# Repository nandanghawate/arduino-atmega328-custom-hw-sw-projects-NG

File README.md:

# atmega328-door-status-alarm-NG
# README #
### What is this repository for? ###

* In this Repo I will be uploading the schematics, pcb layouts, and test codes for the atmega328-door-status-alarm-NG project.
* When door is kept open for more than 10 seconds the device will create an alarm.

### How do I get set up? ###

* I have used Fritzing software for initial Dev board level circuit design or schematic.
* Download and Install Fritzing - https://fritzing.org/download , https://github.com/fritzing/fritzing-app
* I have used  Diptrace for schematics and PCB layouts
* Download and Install Diptrace freeware https://diptrace.com/download/download-diptrace/ 
* I have used Arduino IDE 1.8.19 for programming
* Download and Install Arduino IDE - https://www.arduino.cc/en/software

### Who do I talk to? ###

* Repository is owned and managed by Nandan Ghawate.
* Nandan can also be reached at nandan.ghawate@gmail.com
* https://nandanghawate.com

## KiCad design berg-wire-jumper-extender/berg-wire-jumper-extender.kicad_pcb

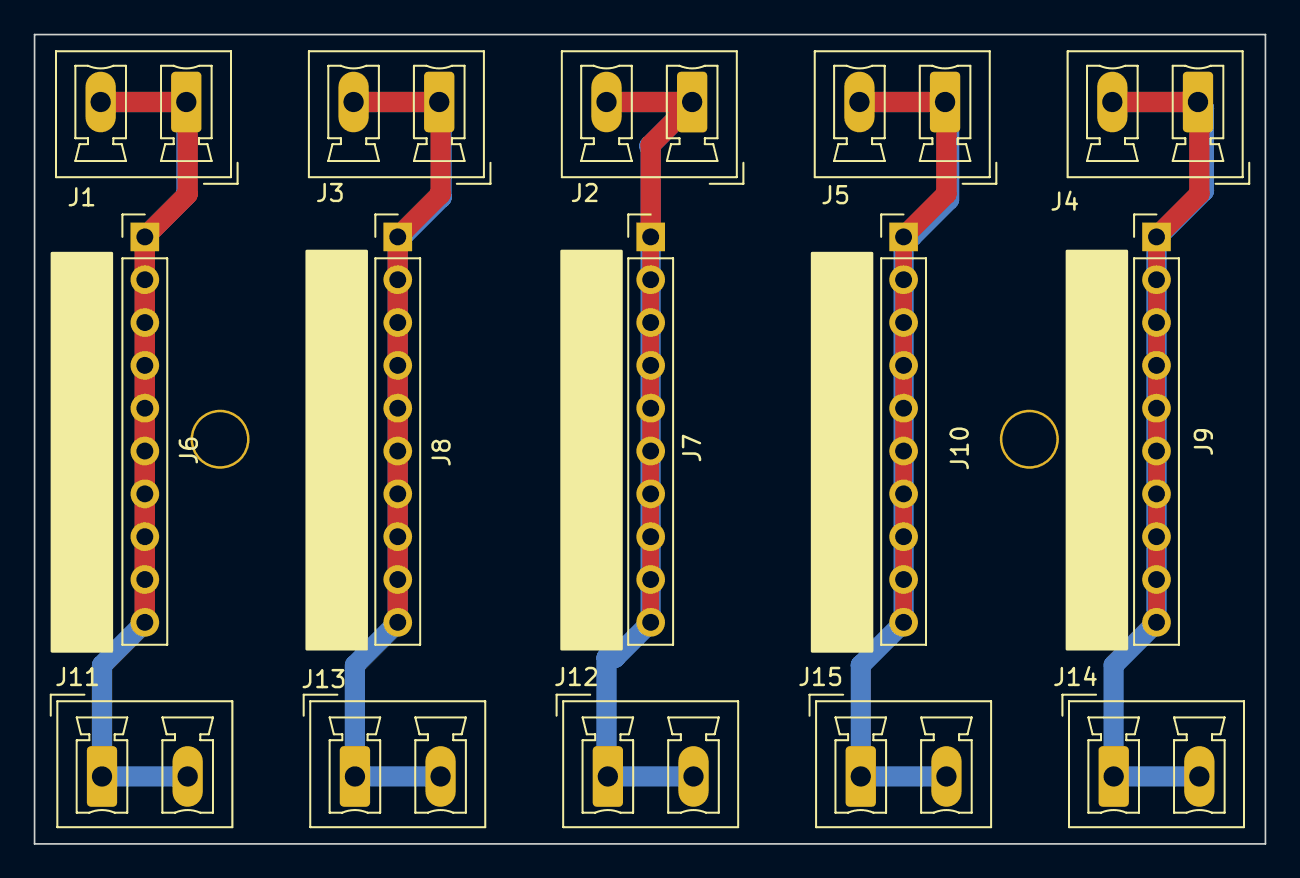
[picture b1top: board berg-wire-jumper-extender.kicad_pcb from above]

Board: 2 copper layers, 73.0 x 48.0 mm, 16 parts (1 on the bottom side), 5 nets.

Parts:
J1, J2, J3, J4, J5, J11, J12, J13, J14, J15: Screw_Terminal_01x02; PhoenixContact_MCV_1,5_2-G-5.08_1x02_P5.08mm_Vertical
J6, J7, J8, J9, J10: Conn_01x10; PinHeader_1x10_P2.54mm_Vertical
NG: LOGO

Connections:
unnamed: J1.1, J1.2, J6.1, J6.2, J6.3, J6.4, J6.5, J6.6, J6.7, J6.8, J6.9, J6.10, J11.1, J11.2
unnamed: J3.1, J3.2, J8.1, J8.2, J8.3, J8.4, J8.5, J8.6, J8.7, J8.8, J8.9, J8.10, J13.1, J13.2
unnamed: J2.1, J2.2, J7.1, J7.2, J7.3, J7.4, J7.5, J7.6, J7.7, J7.8, J7.9, J7.10, J12.1, J12.2
unnamed: J5.1, J5.2, J10.1, J10.2, J10.3, J10.4, J10.5, J10.6, J10.7, J10.8, J10.9, J10.10, J15.1, J15.2
unnamed: J4.1, J4.2, J9.1, J9.2, J9.3, J9.4, J9.5, J9.6, J9.7, J9.8, J9.9, J9.10, J14.1, J14.2

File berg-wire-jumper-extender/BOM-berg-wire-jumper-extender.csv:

Id,Designator,Package,Quantity,Designation,Supplier and ref
1,"J14,J1,J13,J11,J3,J5,J2,J4,J15,J12","PhoenixContact_MCV_1,5_2-G-5.08_1x02_P5.08mm_Vertical",10,Screw_Terminal_01x02,
2,"J10,J7,J8,J9,J6",PinHeader_1x10_P2.54mm_Vertical,5,Conn_01x10,

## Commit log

2022-02-25 Update README.md
    - Updated README.md from specific project to set of projects
2022-02-25 Created atmega328-door-status-alarm Project
2022-02-25 Updated PCB Layout
    - added component values
    - added ground pour
    - updated mounting holes
    - added gerber
2022-02-28 Created Test Code for the Project
    - added Ultrasonic header file.
    - created test code for header file.
2022-04-09 Created Connection Diagram
2022-05-17 Created 1st Test code for PID
    - used Modbus Master Library
    - Reading Raw register data
2022-07-15 completed extender pcb
2022-07-21 Generated BOM and CPL files
